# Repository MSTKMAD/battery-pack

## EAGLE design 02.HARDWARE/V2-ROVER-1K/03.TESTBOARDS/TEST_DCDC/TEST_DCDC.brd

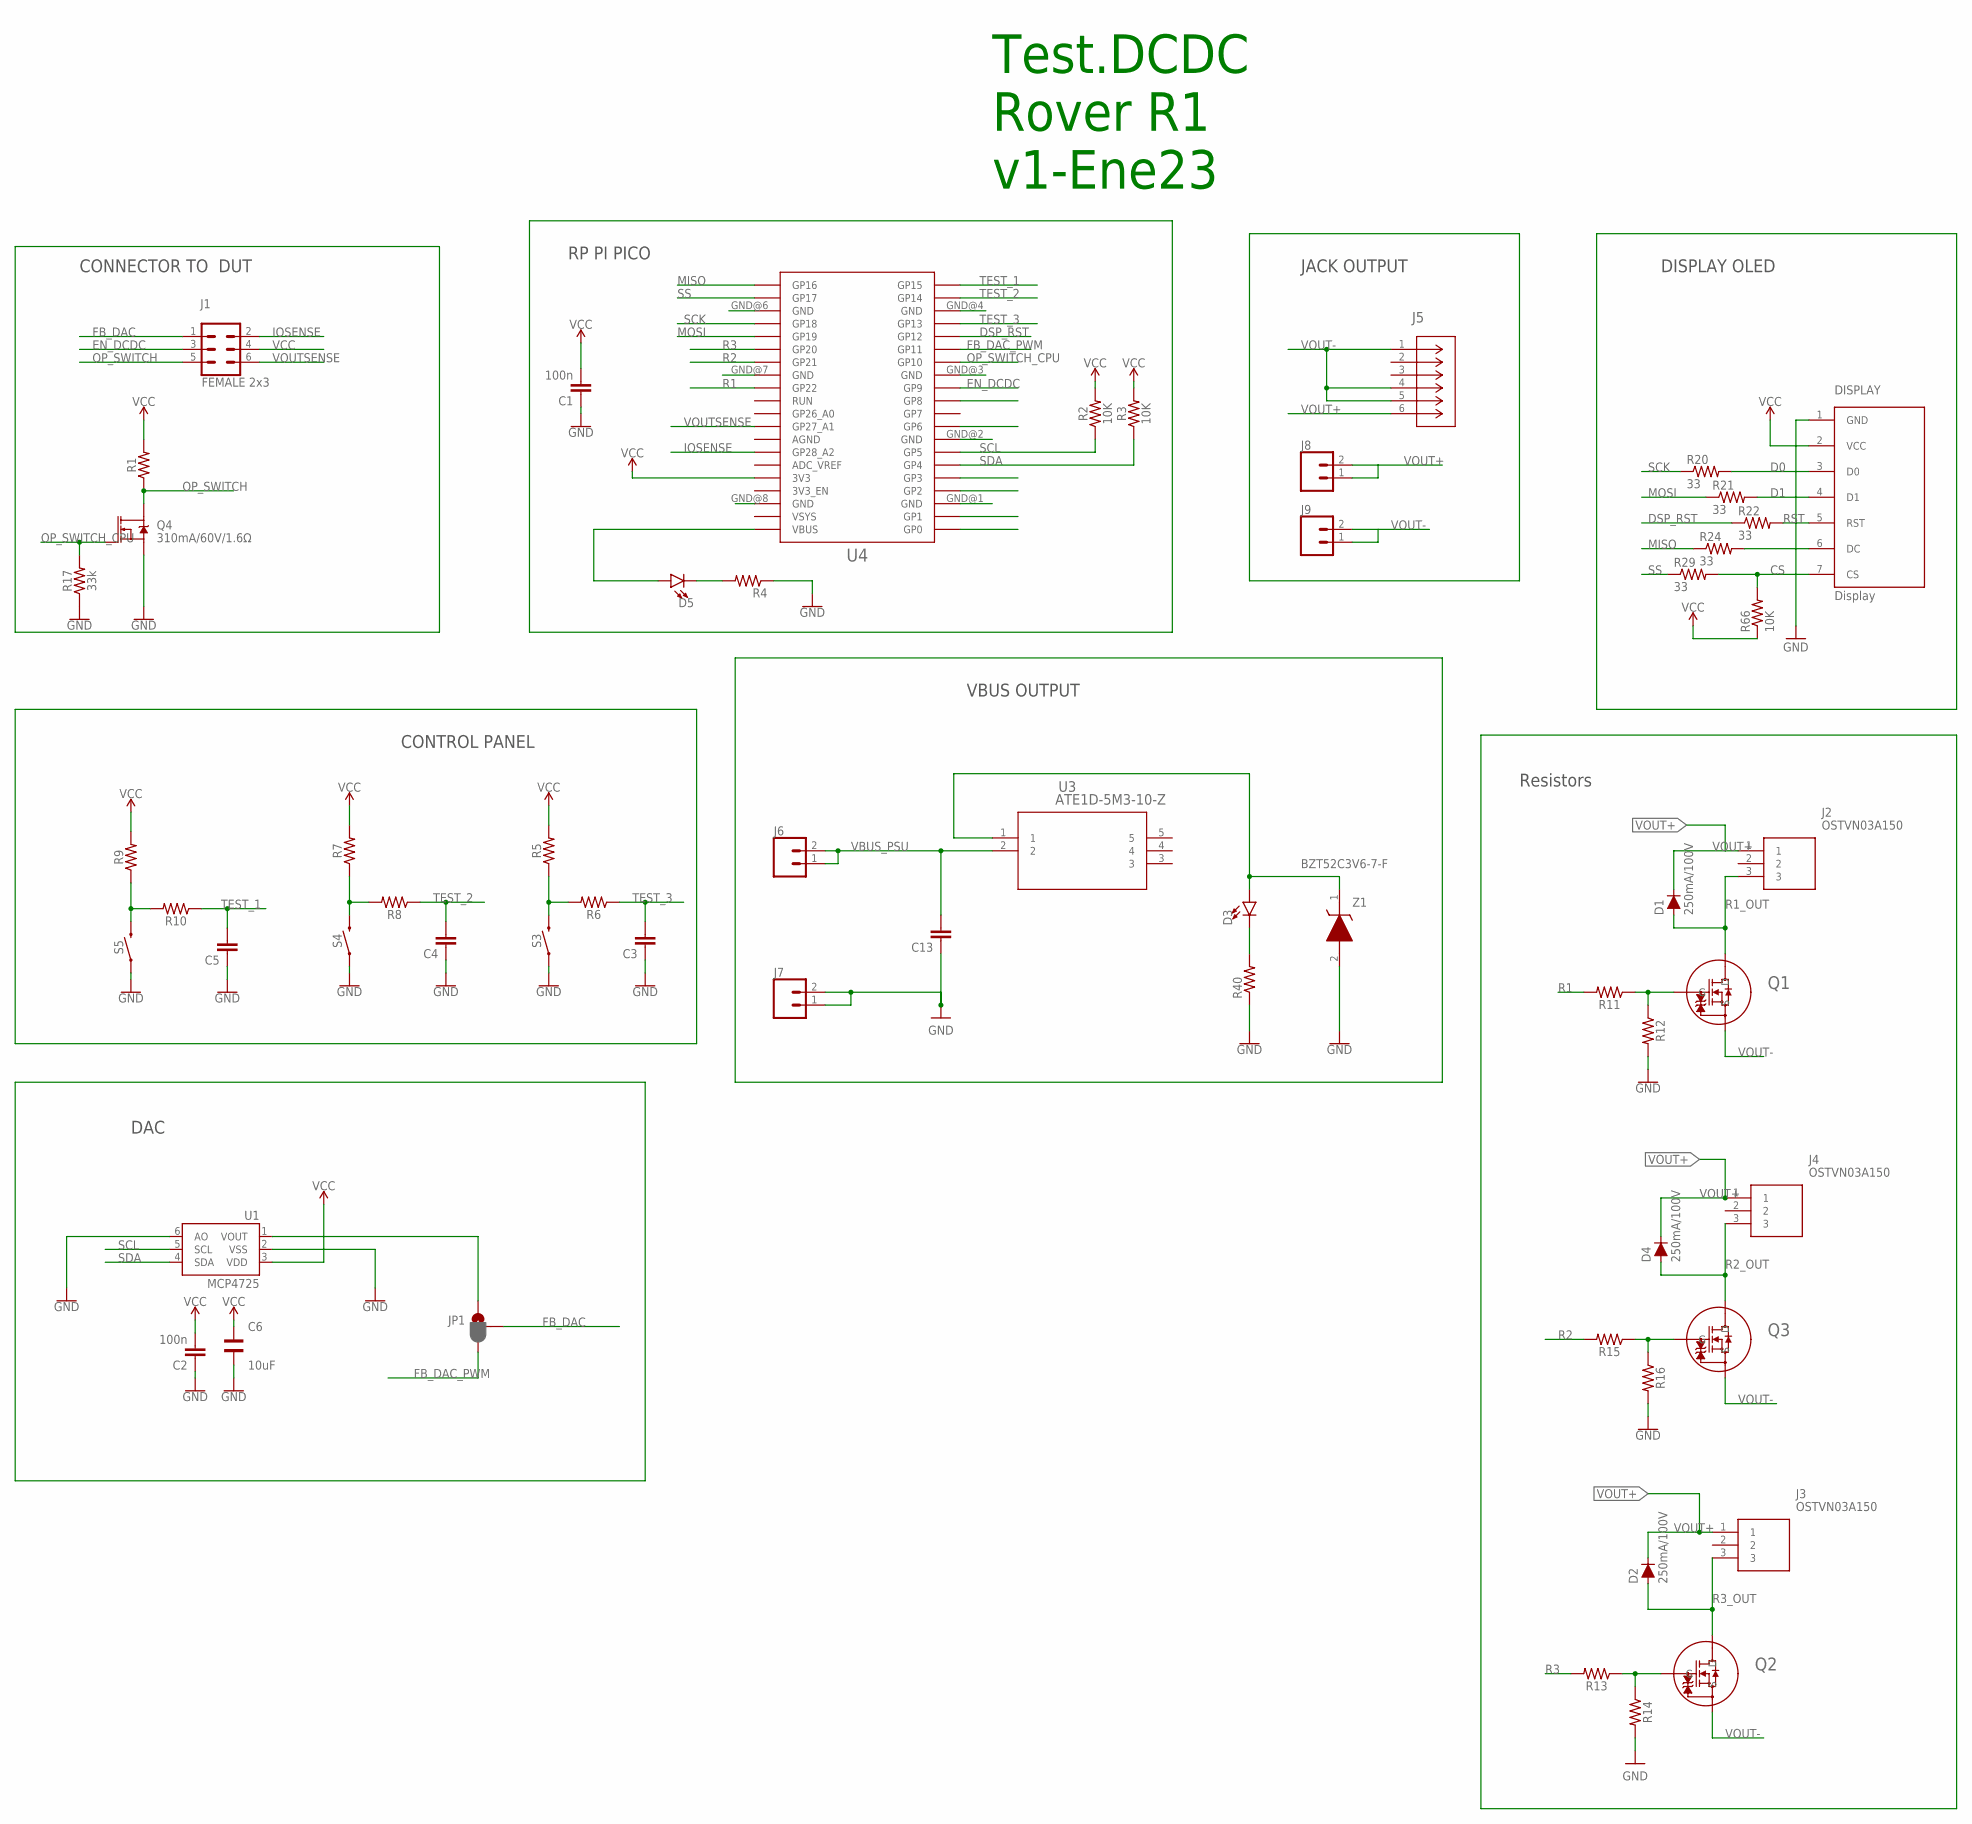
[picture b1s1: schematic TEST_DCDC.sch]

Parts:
C1, C2: 100n; C0805
C3, C4, C5, C13: C-EUC0805; C0805
C6: 10uF; WCAP-CSGP_1206
D1, D2, D4: 250mA/100V; SOD-323
D3, D5: LED3MM; LED_3MM
DISPLAY: Display; OLED_LCD
J1: FEMALE 2x3; 2X3
J2, J3, J4: OSTVN03A150
J5: ACJS-MHDR; CONN_MHDR_AMP
J6, J7, J8, J9: CONN_02; 1X02
JP1: JUMPER-SMT_3_1-NC_PASTE_SILK; SMT-JUMPER_3_1-NC_PASTE_SILK
Q1, Q2, Q3: PJA3416AE_R1_00001; SOT23_PJA3416_PNJ
Q4: 310mA/60V/1.6Ω; SOT323
R1, R5, R6, R7, R8, R9, R10, R11, R12, R13, R14, R15, R16: 0805
R2, R3, R4, R40, R66: 10K; 0805
R17: 33k; 0805
R20, R21, R22, R24, R29: 33; 0805
S3, S4, S5: MOMENTARY-SWITCH-SPST-SMD-5.2MM; TACTILE_SWITCH_SMD_5.2MM
U1: MCP4725; SOT23-6
U3: ATE1D-5M3-10-Z; SPDT05_ATE1D_9P5X8_NDC
U4: RPI_PICO_IG-TH; RPI_PICO_TH
Z1: BZT52C3V6-7-F; SOD3716X135N

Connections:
CS: DISPLAY.7 (CS), R29.2, R66.2
D0: DISPLAY.3 (D0), R20.2
D1: DISPLAY.4 (D1), R21.2
DSP_RST: R22.1, U4.GP12
EN_DCDC: J1.3, U4.GP9
FB_DAC: J1.1, JP1.2
FB_DAC_PWM: JP1.3, U4.GP11
GND: C1.1, C2.1, C3.1, C4.1, C5.1, C6.1, C13.1, DISPLAY.1 (GND), J7.1, J7.2, Q4.2 (S), R4.1, R12.2, R14.2, R16.2, R17.1, R40.1, S3.1, S4.1, S5.1, U1.2 (VSS), U1.6 (AO), U4.GND@1 (GND), U4.GND@2 (GND), U4.GND@3 (GND), U4.GND@4 (GND), U4.GND@6 (GND), U4.GND@7 (GND), U4.GND@8 (GND), Z1.2 (A)
IOSENSE: J1.2, U4.GP28_A2
MISO: R24.1, U4.GP16
MOSI: R21.1, U4.GP19
unnamed: R5.1, R6.2, S3.3 (2)
unnamed: R7.1, R8.2, S4.3 (2)
unnamed: R9.1, R10.2, S5.3 (2)
unnamed: DISPLAY.6 (DC), R24.2
unnamed: JP1.1, U1.1 (VOUT)
unnamed: Q1.1 (G), R11.1, R12.1
unnamed: Q2.1 (G), R13.1, R14.1
unnamed: D5.K (C), R4.2
unnamed: D5.A, U4.VBUS
unnamed: D3.K (C), R40.2
unnamed: Q3.1 (G), R15.1, R16.1
OP_SWITCH: J1.5, Q4.3 (D), R1.1
OP_SWITCH_CPU: Q4.1 (G), R17.2, U4.GP10
R1: R11.2, U4.GP22
R1_OUT: D1.A, J2.3, Q1.3 (D)
R2: R15.2, U4.GP21
R2_OUT: D4.A, J4.3, Q3.3 (D)
R3: R13.2, U4.GP20
R3_OUT: D2.A, J3.3, Q2.3 (D)
RST: DISPLAY.5 (RST), R22.2
SCK: R20.1, U4.GP18
SCL: R2.1, U1.5 (SCL), U4.GP5
SDA: R3.1, U1.4 (SDA), U4.GP4
SS: R29.1, U4.GP17
TEST_1: C5.2, R10.1, U4.GP15
TEST_2: C4.2, R8.1, U4.GP14
TEST_3: C3.2, R6.1, U4.GP13
VBUS: D3.A, U3.1, Z1.1 (K)
VBUS_PSU: C13.2, J6.1, J6.2, U3.2
VCC: C1.2, C2.2, C6.2, DISPLAY.2 (VCC), J1.4, R1.2, R2.2, R3.2, R5.2, R7.2, R9.2, R66.1, U1.3 (VDD), U4.3V3
VOUT+: D1.C, D2.C, D4.C, J2.1, J3.1, J4.1, J5.6, J8.1, J8.2
VOUT-: J5.1, J5.4, J5.5, J9.1, J9.2, Q1.2 (S), Q2.2 (S), Q3.2 (S)
VOUTSENSE: J1.6, U4.GP27_A1

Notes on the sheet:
Test.DCDC Rover R1 v1-Ene23
CONTROL PANEL
VBUS OUTPUT
Resistors
DISPLAY OLED
RP PI PICO
DAC
CONNECTOR TO DUT
JACK OUTPUT

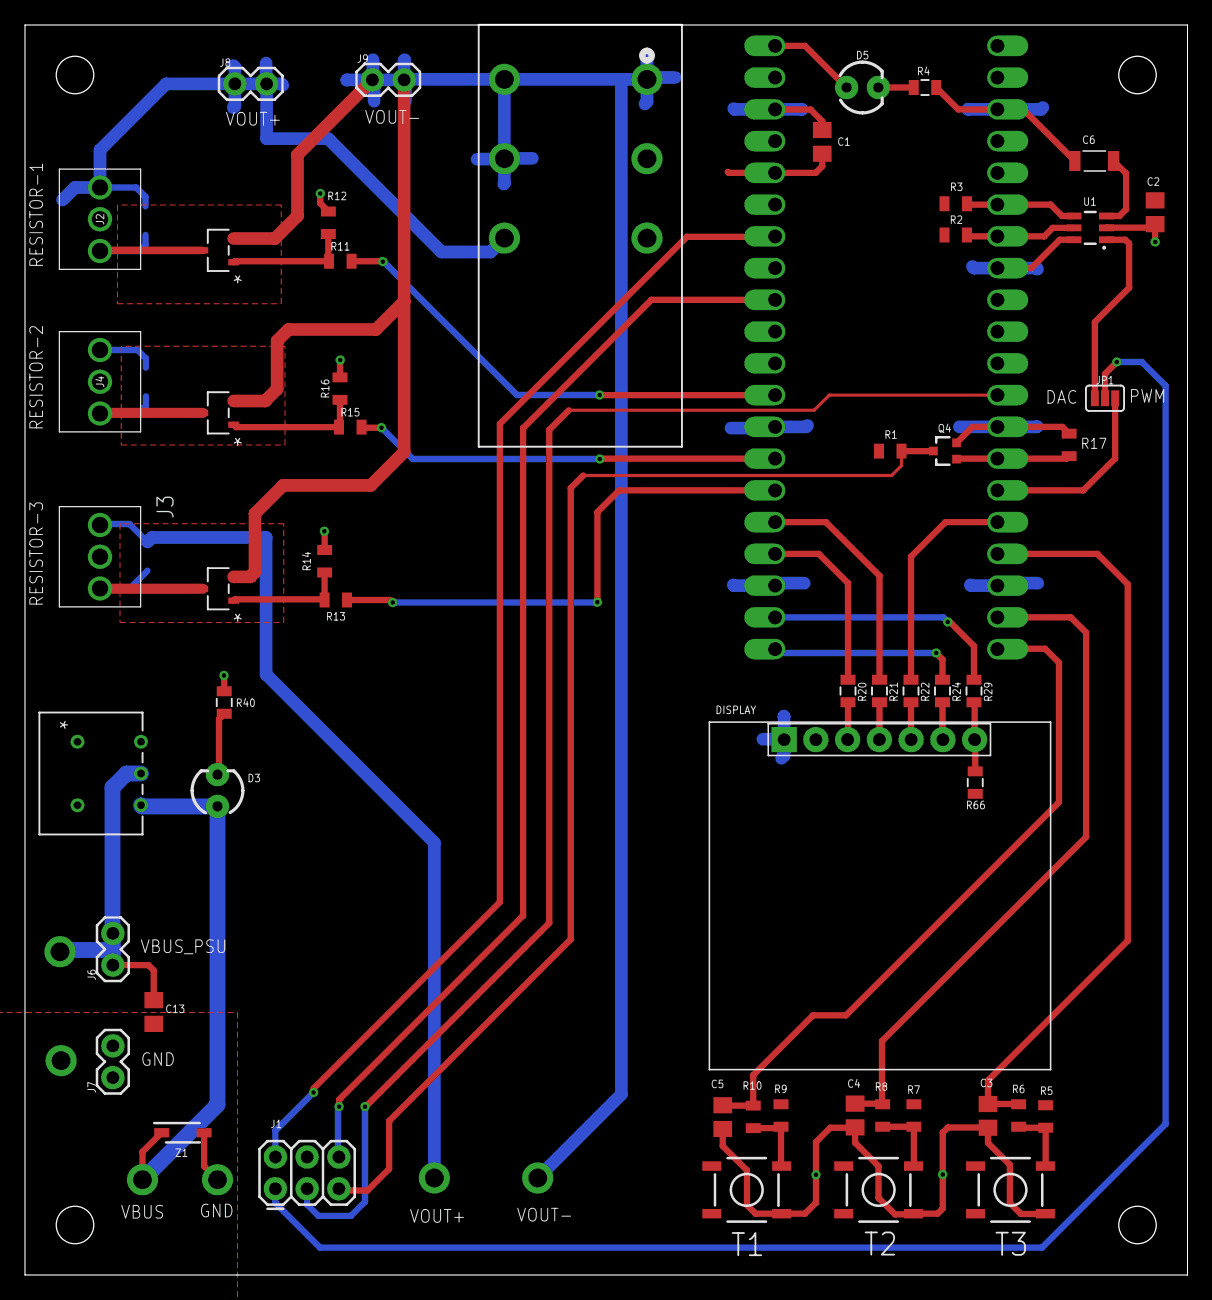
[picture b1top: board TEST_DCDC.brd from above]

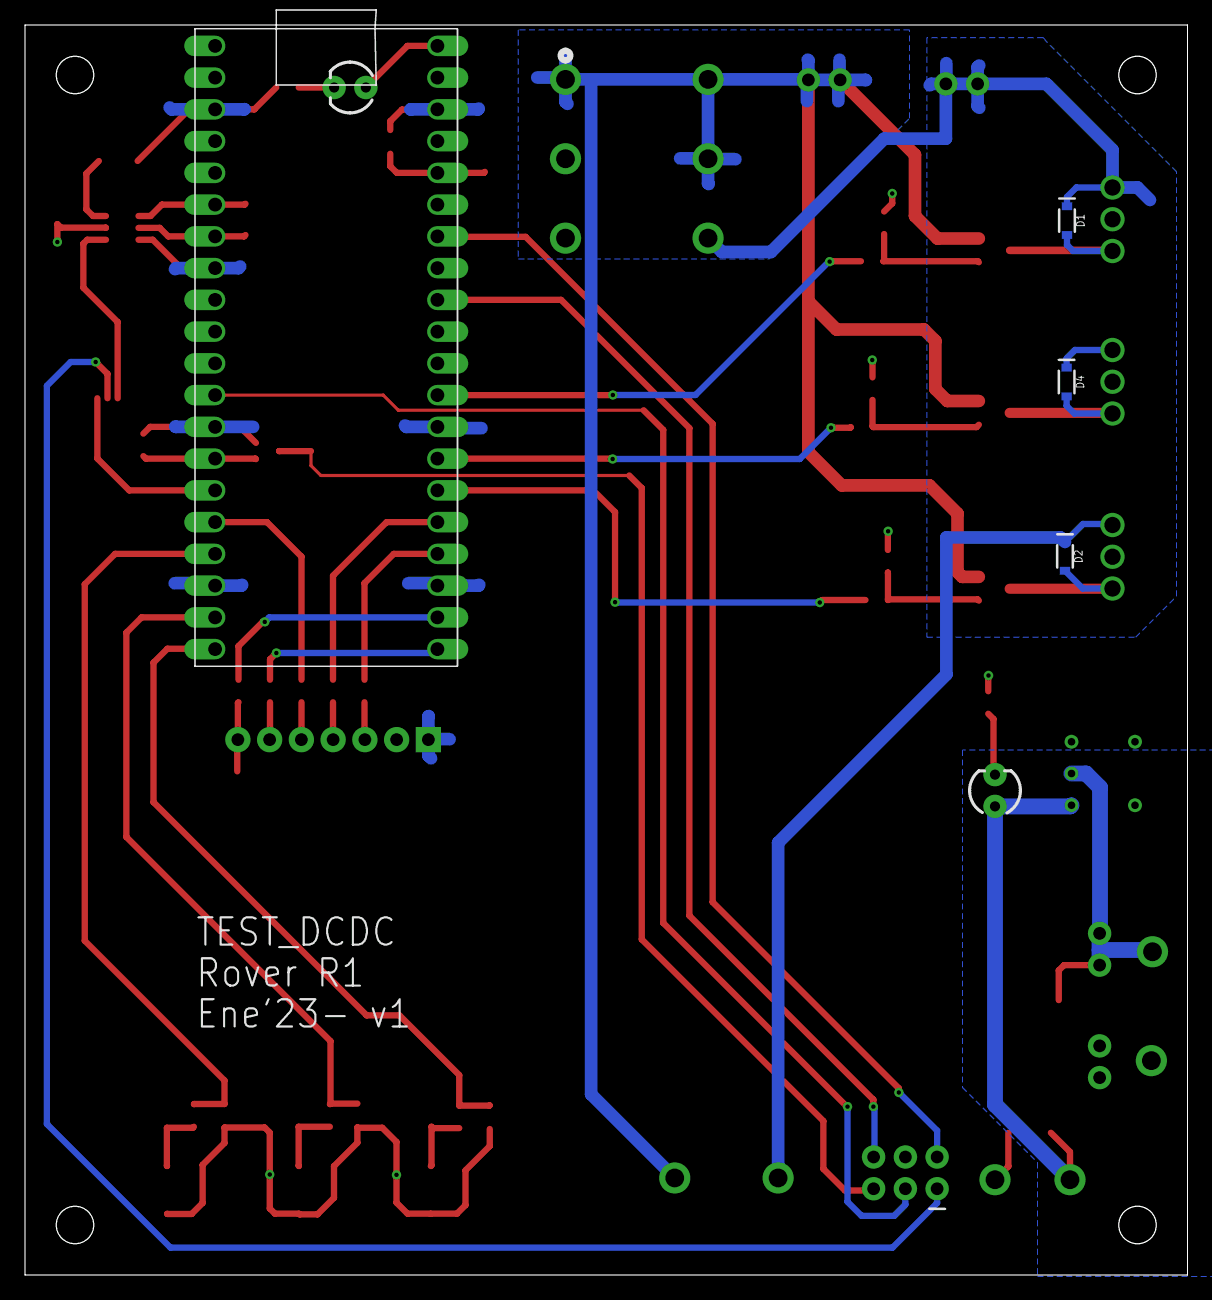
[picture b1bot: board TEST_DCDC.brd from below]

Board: 2 copper layers, 93.0 x 100.0 mm, 58 parts (4 on the bottom side), 44 nets.

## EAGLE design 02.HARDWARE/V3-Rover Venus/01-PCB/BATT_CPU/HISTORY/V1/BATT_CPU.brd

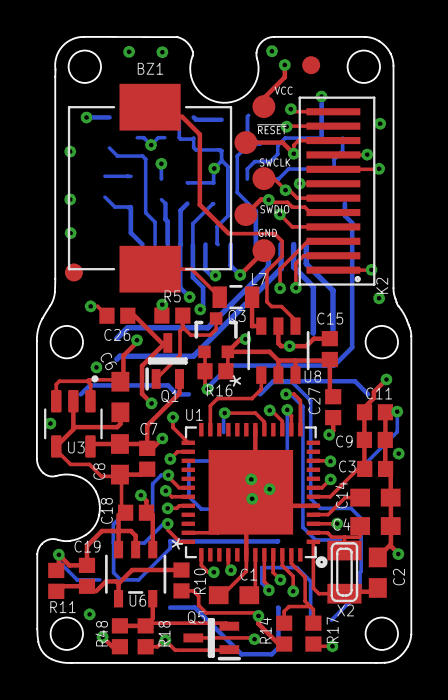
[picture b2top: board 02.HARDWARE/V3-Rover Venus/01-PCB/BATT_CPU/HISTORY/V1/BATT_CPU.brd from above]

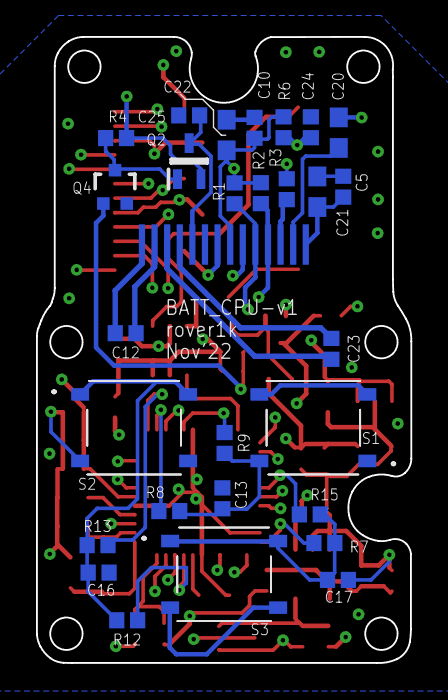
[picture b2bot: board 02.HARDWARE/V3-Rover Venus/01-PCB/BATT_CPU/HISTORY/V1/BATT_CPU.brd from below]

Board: 4 copper layers, 20.8 x 34.8 mm, 70 parts (29 on the bottom side), 45 nets.

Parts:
BZ1: PKMCS0909E4000-R1; PKMCS0909
C1, C6, C8, C14, C20: 2.2uF; 0603
C2, C4: 22pF; 0603-NO
C3, C5, C7, C9, C10, C11, C13, C15, C16, C17, C19, C24, C25, C27: 100n; 0402
C12, C23: 1.0uF; 0402
C18, C26: 100nF; 0402
C21, C22: 4.7uF; 0603
K2: FLEX12; FLEX6
L7: MMZ2012Y202BT000; 0805
Q1, Q2, Q5: BSS84W-7-F; SOT65P222X110-3N
Q3, Q4: 2N7002PW; SOT323
R1, R2, R6: 4k7; 0402
R3: 560k; 0402
R4, R14, R16, R18: 100k; 0402
R5: 47k; 0402
R7, R9, R12: 2k2; 0402
R8, R13, R15: 100R; 0402
R10: 120k; 0402
R11: 8k2; 0402
R17: 150k; 0402
R48: 10k; 0402
S1, S2, S3: PTS526_SKG15_SMTR2_LFS; PTS526SKG15SMTR2LFS
U1: ATSAMD21G18_QFN; TQFN48_7MM
U3: TPS78230DDCR; SOT95P280X110-5N
U6: MAX9062EUK+T; 21-0057F_MXM
U8: SN74LVC1G19DBVR; DBV6
U$30: 64X32_OLED_049; LCD_14_PINS
U$34, U$35: FIDUCIAL""; FIDUCIAL_1MM
VBUS, VBUS1, VBUS2, VBUS3, VBUS4: TESTPAD_TPSQB1,27; TESTPAD_B1,27
X2: 32.768; XTAL3215

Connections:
!CPU_OP_SWITCH: Q5.1, R18.2, U1.26
!RESET: C27.1, K2.10, U1.40, VBUS1.TP
!RES_OLED: C24.1, R6.1, U$30.!RES
AREF: C14.1, U1.4
BUZZER: U1.23, U8.1
C1N: C23.1, U$30.C1N
C1P: C23.2, U$30.C1P
C2N: C12.1, U$30.C2N
C2P: C12.2, U$30.C2P
EN_DCDC: K2.4, U1.25
EN_VCC_2: Q3.1, Q4.1, R16.2, U1.15
FB_DAC: K2.1, U1.3
GND: C1.2, C2.2, C3.2, C4.2, C5.2, C6.2, C7.2, C8.2, C9.2, C10.2, C11.2, C13.2, C14.2, C15.2, C16.2, C17.2, C18.2, C19.2, C20.2, C21.2, C22.2, C24.2, C25.2, C26.2, C27.2, K2.2, Q3.2, Q4.2, R3.1, R11.2, R16.1, R17.1, S1.3, S1.4, S2.3, S2.4, S3.3, S3.4, U1.5, U1.18, U1.35, U1.42, U1.THERMAL, U3.2, U3.4, U6.2, U6.3, U8.2, U8.3, U$30.VSS, VBUS4.TP
IOSENSE: K2.8, U1.7
IREF: R3.2, U$30.IREF
unnamed: C17.1, R7.2, R15.1, S3.1, S3.2
unnamed: C13.1, R8.2, R9.2, S1.2
unnamed: C16.1, R12.2, R13.1, S2.1, S2.2
unnamed: Q2.1, Q4.3, R4.2
unnamed: C2.1, U1.1, X2.P$1
unnamed: Q1.1, Q3.3, R5.2
unnamed: C4.1, U1.2, X2.P$2
unnamed: C19.1, R10.1, R11.1, U6.4
unnamed: Q5.2, R18.1, R48.1, U6.5
unnamed: L7.1, U8.6
unnamed: BZ1.1, L7.2
unnamed: BZ1.2, U8.4
OP_SWITCH: K2.11, Q5.3
SCL: R1.1, U1.32, U$30.SCL
SDA: R2.1, U1.31, U$30.SDA
SWCLK: K2.6, U1.45, VBUS2.TP
SWDIO: K2.5, U1.46, VBUS3.TP
S_DOWN: R13.2, U1.13
S_POWER: R15.2, U1.30
S_UP: R8.1, U1.14
TXO: K2.7, U1.37
VBAT_LCD: C25.1, Q2.3, U$30.VBAT
VBUS: C6.1, K2.3, Q2.2, R4.1, R10.2, R14.1, U3.1, U3.3
VCC: C3.1, C7.1, C8.1, C9.1, C11.1, Q1.2, R5.1, R7.1, R9.1, R12.1, R48.2, U1.6, U1.17, U1.36, U1.44, U3.5, VBUS.TP
VCC_2: C10.1, C15.1, C18.1, C22.1, C26.1, K2.12, Q1.3, R1.2, R2.2, R6.2, U6.1, U8.5, U$30.VDD
VCC_OLED: C5.1, C21.1, U$30.VCC
VCOMH: C20.1, U$30.VCOMH
VDDCORE: C1.1, U1.43
VINSENSE: R14.2, R17.2, U1.47
VOUTSENSE: K2.9, U1.10

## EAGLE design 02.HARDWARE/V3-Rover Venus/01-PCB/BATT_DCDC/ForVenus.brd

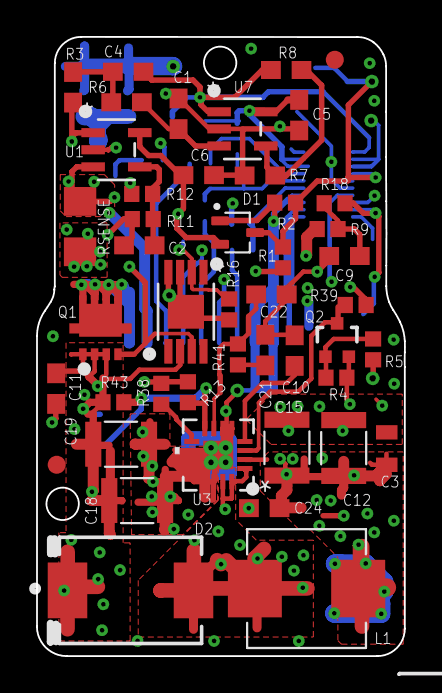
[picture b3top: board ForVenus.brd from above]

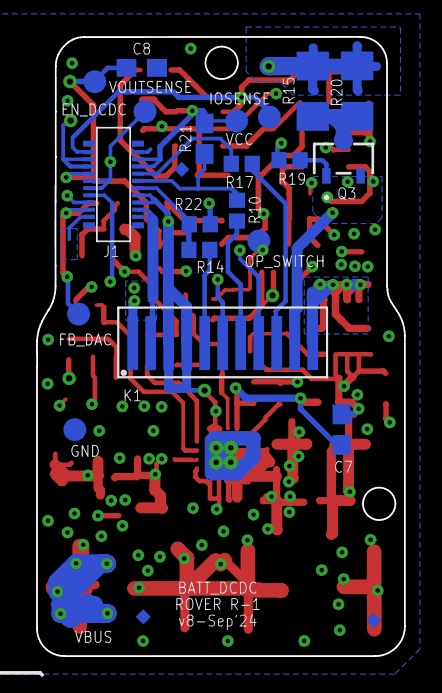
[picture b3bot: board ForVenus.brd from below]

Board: 4 copper layers, 20.4 x 34.4 mm, 70 parts (24 on the bottom side), 36 nets.

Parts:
C1, C4: 1u; 0603-NO
C2, C5, C6, C8, C11: 100n; 0603
C3: 10uF; 0805
C7: 220pF; 0603
C9: N.A.; 0603
C10, C21: 47nF; 0603
C12, C15: 47uF 16V; WCAP-CSGP_1210
C18, C19: 47uF 25V; WCAP-CSGP_1210
C22: 100pF; 0603
C24: 100nF; 0603
D1: BAT54SW,115; SOT65P210X110-3N
D2: B520C-13-F; DIOM7959X250N
EN_DCDC: TESTPAD_TPSQB1,27; TESTPAD_B1,27
FB_DAC: TESTPAD_TPSQB1,27; TESTPAD_B1,27
FD_1, FD_2, FD_3: FD_1; TP06SQ
GND: TESTPAD_TPSQB1,27; TESTPAD_B1,27
IOSENSE: TESTPAD_TPSQB1,27; TESTPAD_B1,27
J1: DF40C-20DP-0.4V_51_; DF40C-20DPA
K1: FLEX11
L1: 2.2uH - 74437346022; INDM7366X500
OP_SWITCH: TESTPAD_TPSQB1,27; TESTPAD_B1,27
Q1: NVTFS9D6P04M8LTAG; NVTFS5124PLTWG
Q2: 2N7002PW; SOT323
Q3: DMN3023L-7; SOT23-TO-236AB_NEX-L
R1: 169k; 0402
R2: 39k; 0402
R3: 2k4; 0603
R4: 100k; 0402
R5, R19: 33R; 0402
R6: 62k; 0603
R7, R21: 4k3; 0603
R8: 36k; 0603
R9: 5k6; 0402
R10, R14, R17: 100R; 0402
R11: 5k1; 0402
R12: 8k2; 0402
R13: 7k5; 0402
R15, R20: 20R; 1206
R16: 10k; 0402
R18: 0R; 0402
R22: 4k3; 0402
R38, R39: 78k7; 0402
R41: 15k; 0402
R43: 30k; 0402
RSENSE: 100mR; 1206
U1, U7: MCP6071T-E/OT; SOT-23-5_MC_MCH
U2: LM5111-4MY/NOPB; MUY08A
U3: TPS55330RTET; RTE16_1P66X1P66_TEX
U$1, U$2: FIDUCIAL""; FIDUCIAL_1MM
VBUS: TESTPAD_TPSQB1,27; TESTPAD_B1,27
VCC: TESTPAD_TPSQB1,27; TESTPAD_B1,27
VOUTSENSE: TESTPAD_TPSQB1,27; TESTPAD_B1,27

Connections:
!RESET: J1.8, R17.1
COMP_TPS: C22.2, R41.1, U3.7
EN_DCDC: EN_DCDC.TP, J1.9, J1.11, R5.2
EN_TPS: Q2.3, R39.2, U3.3
FB: C7.1, R9.1, R13.1, R43.2, U3.8
FB_DAC: FB_DAC.TP, J1.17, R18.2
FREQ_TPS: R38.2, U3.9
GND: C1.2, C3.1, C5.2, C6.2, C8.2, C9.2, C10.2, C11.2, C12.1, C15.1, C18.1, C19.1, C21.1, C22.1, C24.1, D1.1, GND.TP, J1.2, J1.14, J1.16, K1.3, K1.4, Q2.2, R2.2, R4.1, R7.2, R12.2, R13.2, R16.2, R38.1, RSENSE.1, U1.2, U2.3, U2.4, U2.9, U3.5, U3.6, U3.10, U3.11, U3.12, U3.13, U3.14, U3.17, U7.2
IOSENSE: C4.2, IOSENSE.TP, J1.1, R8.1, U7.1
ISENSE_RAW: C2.1, R3.2, R11.1, U1.1
unnamed: C2.2, R11.2, R12.1, U1.4
unnamed: R7.1, R8.2, U7.4
unnamed: C4.1, R3.1, R6.2
unnamed: Q2.1, R4.2, R5.1
unnamed: C1.1, R6.1, U7.3
unnamed: K1.8, R10.2
unnamed: Q3.3, R15.1, R20.1
unnamed: Q1.4, R19.1, U2.7
unnamed: K1.10, R17.2
unnamed: K1.5, R14.2
unnamed: C9.1, R9.2, R18.1
unnamed: Q3.1, R19.2
unnamed: C10.1, U3.4
unnamed: C21.2, R41.2
OP_SWITCH: J1.3, J1.5, OP_SWITCH.TP, R16.1, U2.2
RXI: J1.15, K1.9
SW2_TPS: D2.A, L1.2, U3.1, U3.15, U3.16
SWCLK: J1.10, R10.1, R21.1
SWDIO: J1.12, R14.1, R22.1
TXO: J1.13, K1.7
VBUS: C3.2, C12.2, C15.2, C24.2, J1.18, J1.20, K1.1, K1.2, L1.1, U3.2, VBUS.TP
VCC: C5.1, C6.1, D1.2, J1.4, J1.6, R21.2, R22.2, R39.1, U1.5, U7.5, VCC.TP
VOUT+: K1.12, Q1.5, Q1.6, Q1.7, Q1.8, Q1.9, Q1.10, Q1.11, R1.1, R15.2, R20.2
VOUT-: K1.11, Q3.2, RSENSE.2, U1.3
VOUTSENSE: C8.1, D1.3, J1.7, R1.2, R2.1, VOUTSENSE.TP
VSOURCE: C7.2, C11.1, C18.2, C19.2, D2.C, Q1.1, Q1.2, Q1.3, R43.1, U2.6

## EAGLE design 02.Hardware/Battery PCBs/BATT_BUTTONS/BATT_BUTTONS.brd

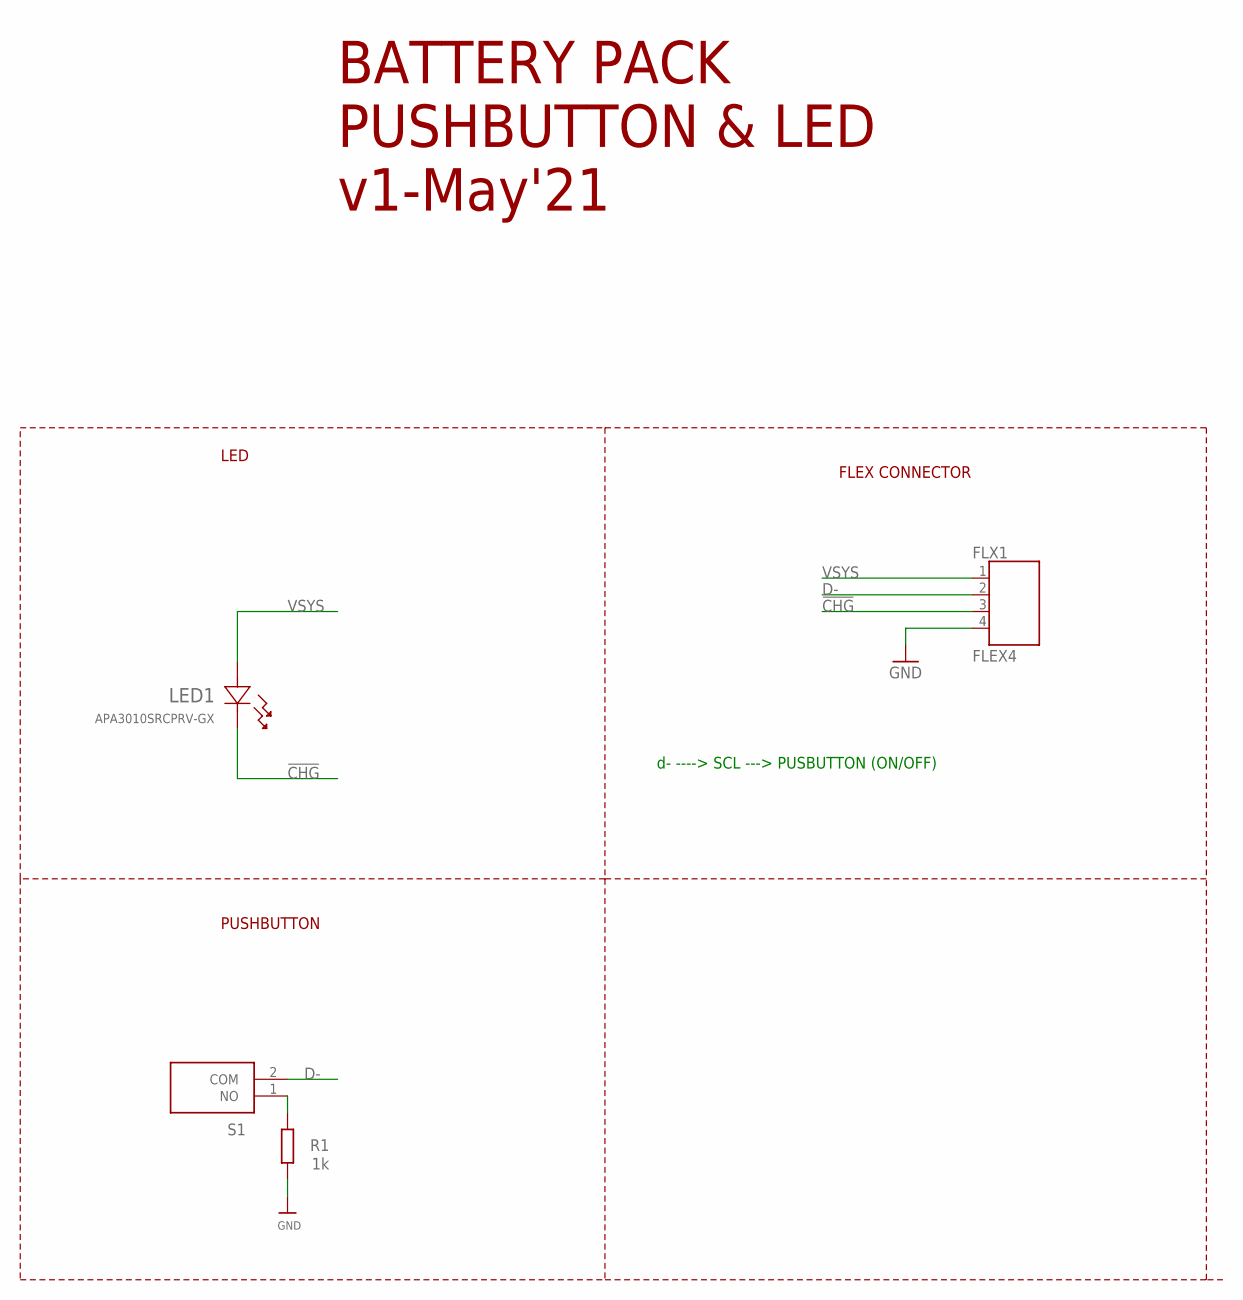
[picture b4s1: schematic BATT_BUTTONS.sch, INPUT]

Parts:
FLX1: FLEX4
LED1: APA3010SRCPRV-GX; LED_APA3010SRCPRV-GX_KNB
R1: 1k; R0603
S1: KXT311LHS

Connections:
!CHG!: FLX1.3, LED1.1
D-: FLX1.2, S1.2 (COM)
GND: FLX1.4, R1.1
unnamed: R1.2, S1.1 (NO)
VSYS: FLX1.1, LED1.2

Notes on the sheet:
BATTERY PACK PUSHBUTTON & LED v1-May'21
LED
d- ----> SCL ---> PUSBUTTON (ON/OFF)
FLEX CONNECTOR
PUSHBUTTON

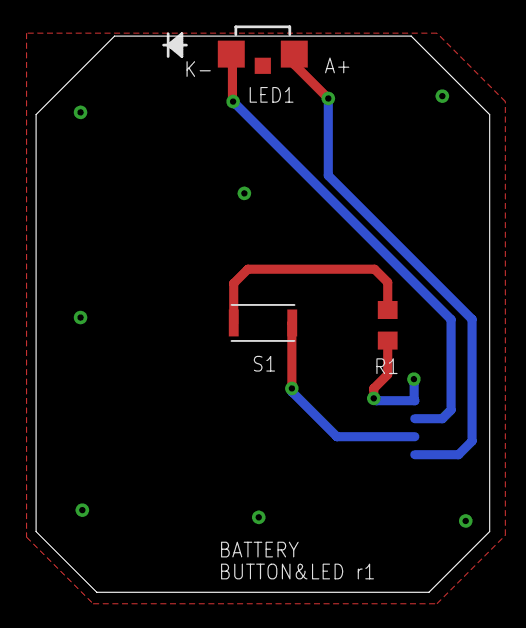
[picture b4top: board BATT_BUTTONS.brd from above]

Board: 2 copper layers, 25.2 x 30.9 mm, 4 parts (1 on the bottom side), 5 nets.

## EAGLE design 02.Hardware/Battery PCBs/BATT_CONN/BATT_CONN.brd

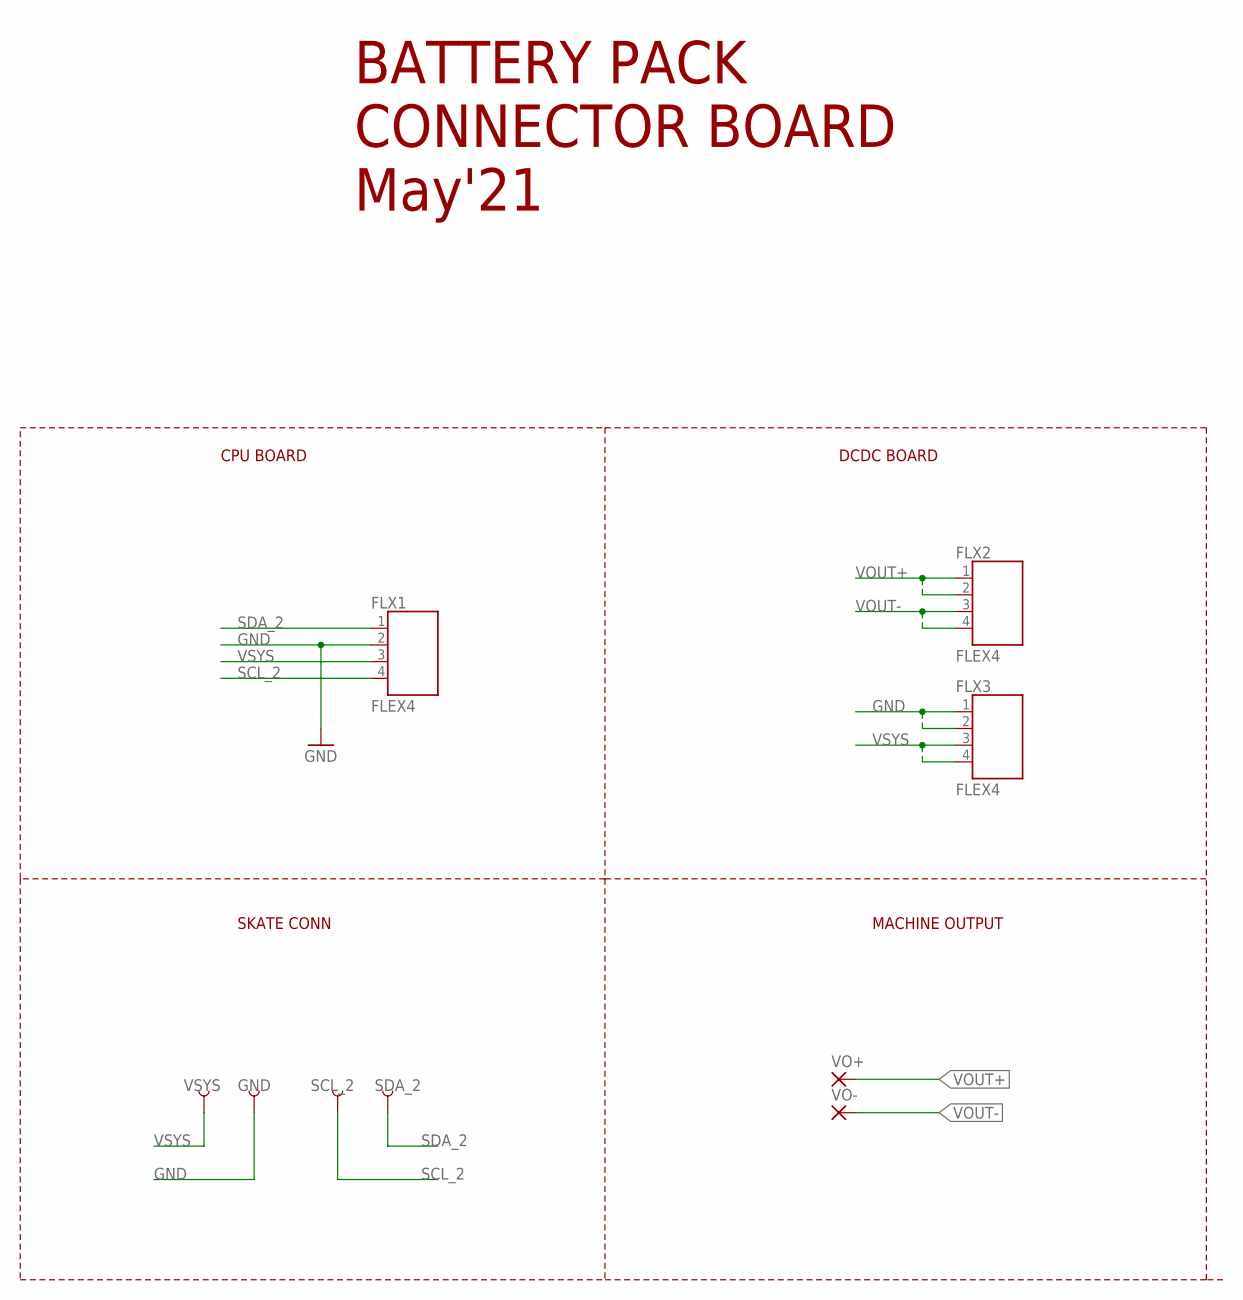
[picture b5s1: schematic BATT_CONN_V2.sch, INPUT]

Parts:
FLX1, FLX2, FLX3: FLEX4
GND: TEST-POINT3; PAD.03X.03
SCL_2: TEST-POINT3; PAD.03X.03
SDA_2: TEST-POINT3; PAD.03X.03
VO+: SMD5; SMD2,54-5,08
VO-: SMD5; SMD2,54-5,08
VSYS: TEST-POINT3; PAD.03X.03

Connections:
GND: FLX1.2, FLX3.1, FLX3.2, GND.P$1
SCL_2: FLX1.4, SCL_2.P$1
SDA_2: FLX1.1, SDA_2.P$1
VOUT+: FLX2.1, FLX2.2, VO+.1
VOUT-: FLX2.3, FLX2.4, VO-.1
VSYS: FLX1.3, FLX3.3, FLX3.4, VSYS.P$1

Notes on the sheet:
BATTERY PACK CONNECTOR BOARD May'21
CPU BOARD
DCDC BOARD
SKATE CONN
MACHINE OUTPUT

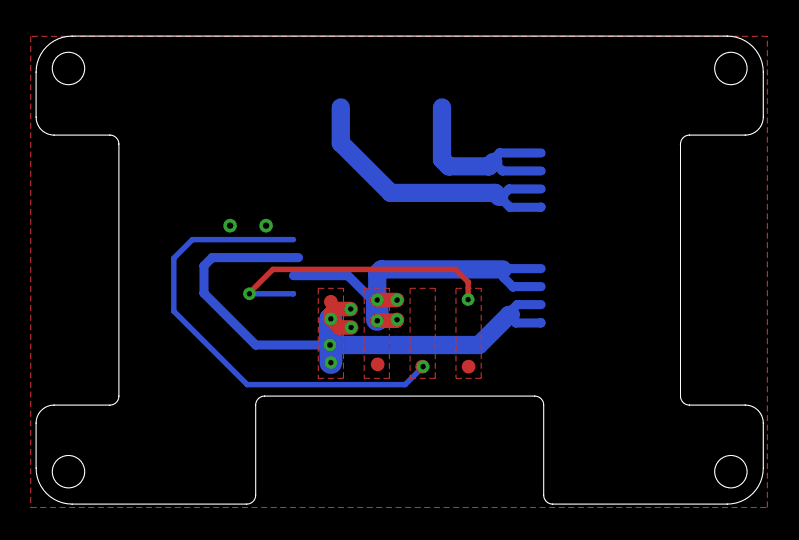
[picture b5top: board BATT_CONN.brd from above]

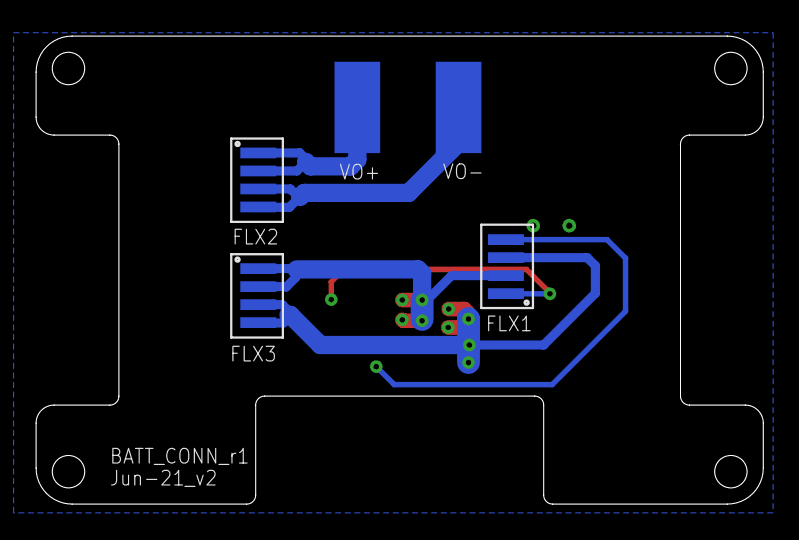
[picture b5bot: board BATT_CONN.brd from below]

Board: 2 copper layers, 40.4 x 26.0 mm, 9 parts (5 on the bottom side), 6 nets.

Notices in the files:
parts and their libraries:
SparkFun-Switches: Licensing: Creative Commons ShareAlike 4.0 International - https://creativecommons.org/licenses/by-sa/4.0
Wurth_Elektronik_Passive_Capacitors_rev1: Copyright: Würth Elektronik
COPYRIGHT: Copyright (C) 2022 Ultra Librarian. All rights reserved.
